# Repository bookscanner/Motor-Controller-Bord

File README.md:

# bookscanner
design of an affordable bookscanner for African universities

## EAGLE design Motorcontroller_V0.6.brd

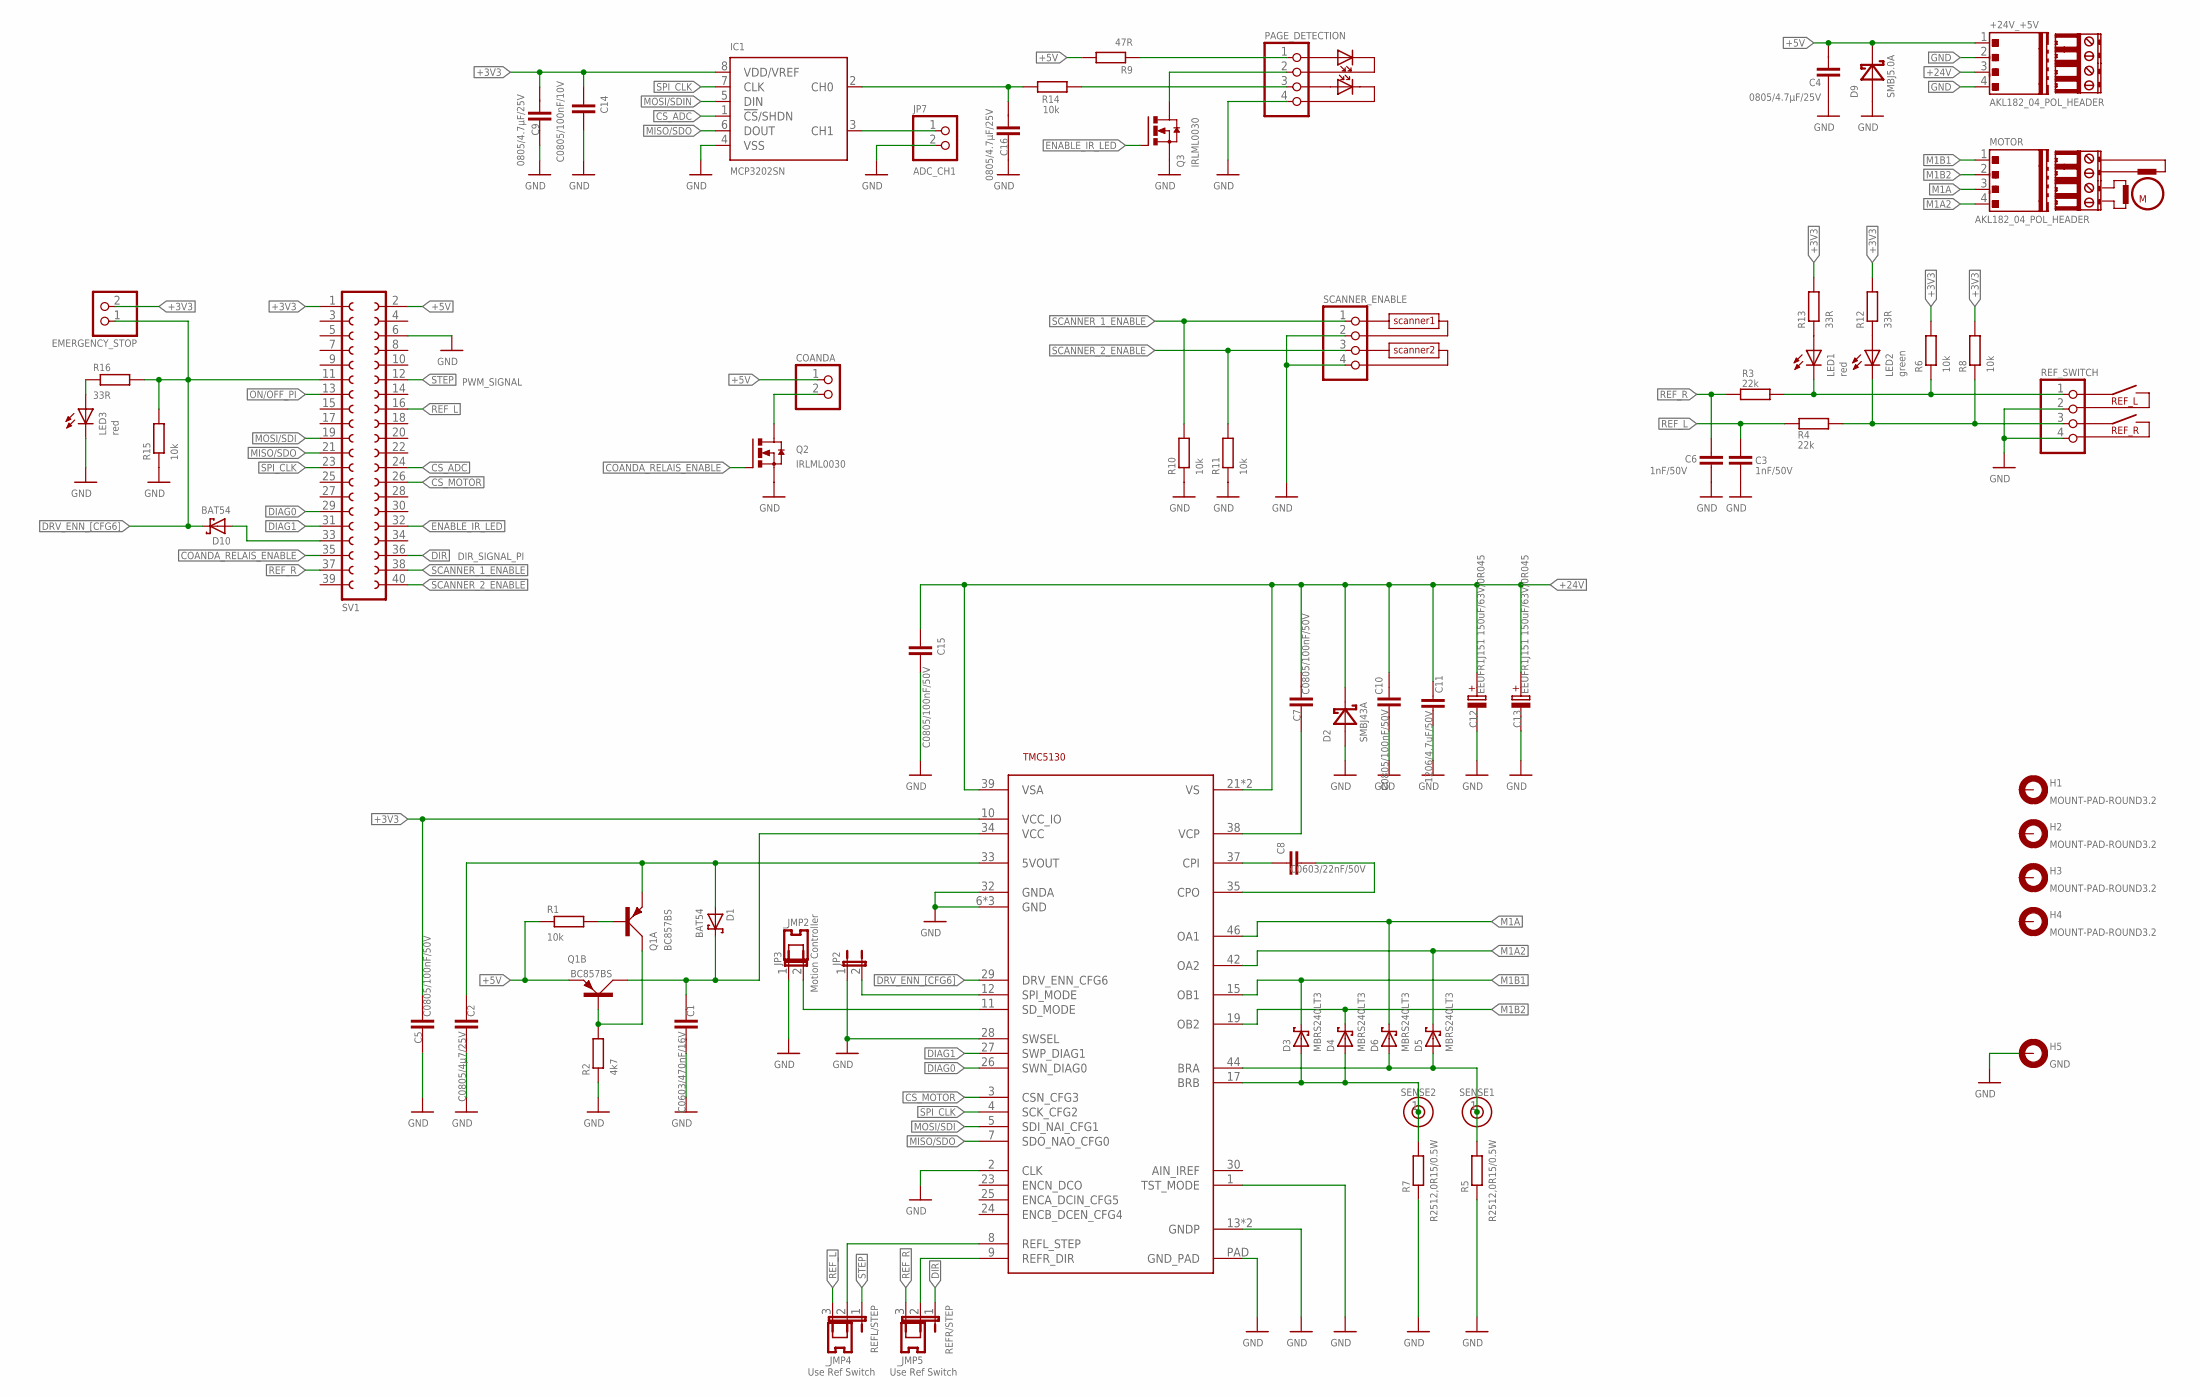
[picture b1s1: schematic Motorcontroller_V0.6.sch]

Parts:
+24V_+5V: AKL182_04_POL_HEADER; AKL169_04_POL
C1: C0603/470nF/16V; 0603
C2: C0805/4µ7/25V; 0805
C3, C6: 1nF/50V; C0603K
C4, C9, C16: 0805/4.7µF/25V; RCL_0805
C5, C7, C10: C0805/100nF/50V; 0805
C8: C0603/22nF/50V; C0603
C11: 1206/4.7uF/50V; C1206
C12, C13: EEUFR1J151 150uF/63V/0R045; C_POL_RAD_THT_5X10X12.5
C14: C0805/100nF/10V; C0805
C15: C0805/100nF/50V; C0805
COANDA: PINHD-1X2; 1X02
D1, D10: BAT54; SOT23
D2: SMBJ43A; SMB
D3, D4, D5, D6: MBRS240LT3; SMB
D9: SMBJ5.0A; SMB
EMERGENCY_STOP: PINHD-1X2; 1X02
H1, H2, H3, H4: MOUNT-PAD-ROUND3.2; 3,2-PAD
H5: GND; 3,2-PAD
IC1: MCP3202SN; SO-08
JP2, JP3: JP1E; JP1
JP7: ADC_CH1; 1X02
LED1, LED3: red; CHIP-LED0805
LED2: green; CHIP-LED0805
MOTOR: AKL182_04_POL_HEADER; AKL169_04_POL
PAGE_DETECTION: PINHD-1X4; 1X04
Q1: BC857BS; SOT363_PHILIPS
Q2, Q3: IRLML0030; SOT-23
R1, R6, R8, R10, R11, R14, R15: 10k; M0805
R2: 4k7; M0805
R3, R4: 22k; R0603
R5, R7: R2512,0R15/0.5W; R2512
R9: 47R; M1206
R12, R13, R16: 33R; M0805
REFL/STEP: JP2E; JP2
REFR/STEP: JP2E; JP2
REF_SWITCH: PINHD-1X4; 1X04
SCANNER_ENABLE: PINHD-1X4; 1X04
SENSE1, SENSE2: 1PIN_1ROW; 1PIN_1ROW_THT
SV1: FE20-2
TERM1, TERM3: AKL182_04_POL_TERMINAL; EXTRA_TERMINAL
TMC5130: TMC5130; QFP50P900X900X113-49N_NOFID

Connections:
+3V3: C5.1, C9.1, C14.2, EMERGENCY_STOP.2, IC1.8 (VDD/VREF), R6.2, R8.2, R12.2, R13.2, SV1.1, TMC5130.10 (VCC_IO)
+5V: +24V_+5V.1, C4.1, COANDA.1, D9.C, Q1.4 (E), R1.1, R9.2, SV1.2
+24V: +24V_+5V.3, C7.1, C10.2, C11.1, C12.+, C13.+, C15.2, D2.C, TMC5130.21 (VS), TMC5130.39 (VSA), TMC5130.40 (VS)
COANDA_RELAIS_ENABLE: Q2.1 (G), SV1.35
CS_ADC: IC1.1 (!CS!/SHDN), SV1.24
CS_MOTOR: SV1.26, TMC5130.3 (CSN_CFG3)
DIAG0: SV1.29, TMC5130.26 (SWN_DIAG0)
DIAG1: SV1.31, TMC5130.27 (SWP_DIAG1)
DIR: REFR/STEP.1, SV1.36
DRV_ENN_[CFG6]: D10.3 (C), EMERGENCY_STOP.1, R15.2, R16.2, SV1.11, TMC5130.29 (DRV_ENN_CFG6)
ENABLE_IR_LED: Q3.1 (G), SV1.32
GND: +24V_+5V.2, +24V_+5V.4, C1.1, C2.1, C3.1, C4.2, C5.2, C6.1, C9.2, C10.1, C11.2, C12.-, C13.-, C14.1, C15.1, C16.2, D2.A, D9.A, H5.B3,2, IC1.4 (VSS), JP2.1, JP3.1, JP7.2, LED3.C, PAGE_DETECTION.4, Q2.2 (S), Q3.2 (S), R2.1, R5.1, R7.1, R10.1, R11.1, R15.1, REF_SWITCH.2, REF_SWITCH.4, SCANNER_ENABLE.2, SCANNER_ENABLE.4, SV1.6, TMC5130.1 (TST_MODE), TMC5130.2 (CLK), TMC5130.6 (GND), TMC5130.13 (GNDP), TMC5130.28 (SWSEL), TMC5130.31 (GND), TMC5130.32 (GNDA), TMC5130.36 (GND), TMC5130.48 (GNDP), TMC5130.PAD (GND_PAD)
GND1: COANDA.2, Q2.3 (D)
M1A: D6.C, MOTOR.3, TMC5130.46 (OA1)
M1A2: D5.C, MOTOR.4, TMC5130.42 (OA2)
M1B1: D3.C, MOTOR.1, TMC5130.15 (OB1)
M1B2: D4.C, MOTOR.2, TMC5130.19 (OB2)
MISO/SDO: IC1.6 (DOUT), SV1.21, TMC5130.7 (SDO_NAO_CFG0)
MOSI/SDI: SV1.19, TMC5130.5 (SDI_NAI_CFG1)
MOSI/SDIN: IC1.5 (DIN)
unnamed: Q1.5 (B), Q1.6 (C), R2.2
unnamed: C1.2, D1.3 (C), Q1.3 (C), TMC5130.34 (VCC)
unnamed: JP2.2, TMC5130.12 (SPI_MODE)
unnamed: Q1.2 (B), R1.2
unnamed: JP3.2, TMC5130.11 (SD_MODE)
unnamed: D10.1 (A), SV1.33
unnamed: LED3.A, R16.1
unnamed: C8.1, TMC5130.37 (CPI)
unnamed: C8.2, TMC5130.35 (CPO)
unnamed: C7.2, TMC5130.38 (VCP)
unnamed: PAGE_DETECTION.2, Q3.3 (D)
unnamed: C2.2, D1.1 (A), Q1.1 (E), TMC5130.33 (5VOUT)
unnamed: REFR/STEP.2, TMC5130.9 (REFR_DIR)
unnamed: REFL/STEP.2, TMC5130.8 (REFL_STEP)
unnamed: LED2.C, R4.2, R8.1, REF_SWITCH.3
unnamed: LED1.C, R3.2, R6.1, REF_SWITCH.1
unnamed: LED2.A, R12.1
unnamed: LED1.A, R13.1
unnamed: C16.1, IC1.2 (CH0), R14.2
unnamed: IC1.3 (CH1), JP7.1
unnamed: PAGE_DETECTION.3, R14.1
unnamed: PAGE_DETECTION.1, R9.1
ON/OFF_PI: SV1.13
REF_L: C3.2, R4.1, REFL/STEP.3, SV1.16
REF_R: C6.2, R3.1, REFR/STEP.3, SV1.37
SCANNER_1_ENABLE: R10.2, SCANNER_ENABLE.1, SV1.38
SCANNER_2_ENABLE: R11.2, SCANNER_ENABLE.3, SV1.40
SENSE1: D5.A, D6.A, R5.2, SENSE1.1, TMC5130.44 (BRA)
SENSE2: D3.A, D4.A, R7.2, SENSE2.1, TMC5130.17 (BRB)
SPI_CLK: IC1.7 (CLK), SV1.23, TMC5130.4 (SCK_CFG2)
STEP: REFL/STEP.1, SV1.12

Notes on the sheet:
REF_L
REF_R
scanner1
scanner2
PWM_SIGNAL
DIR_SIGNAL_PI

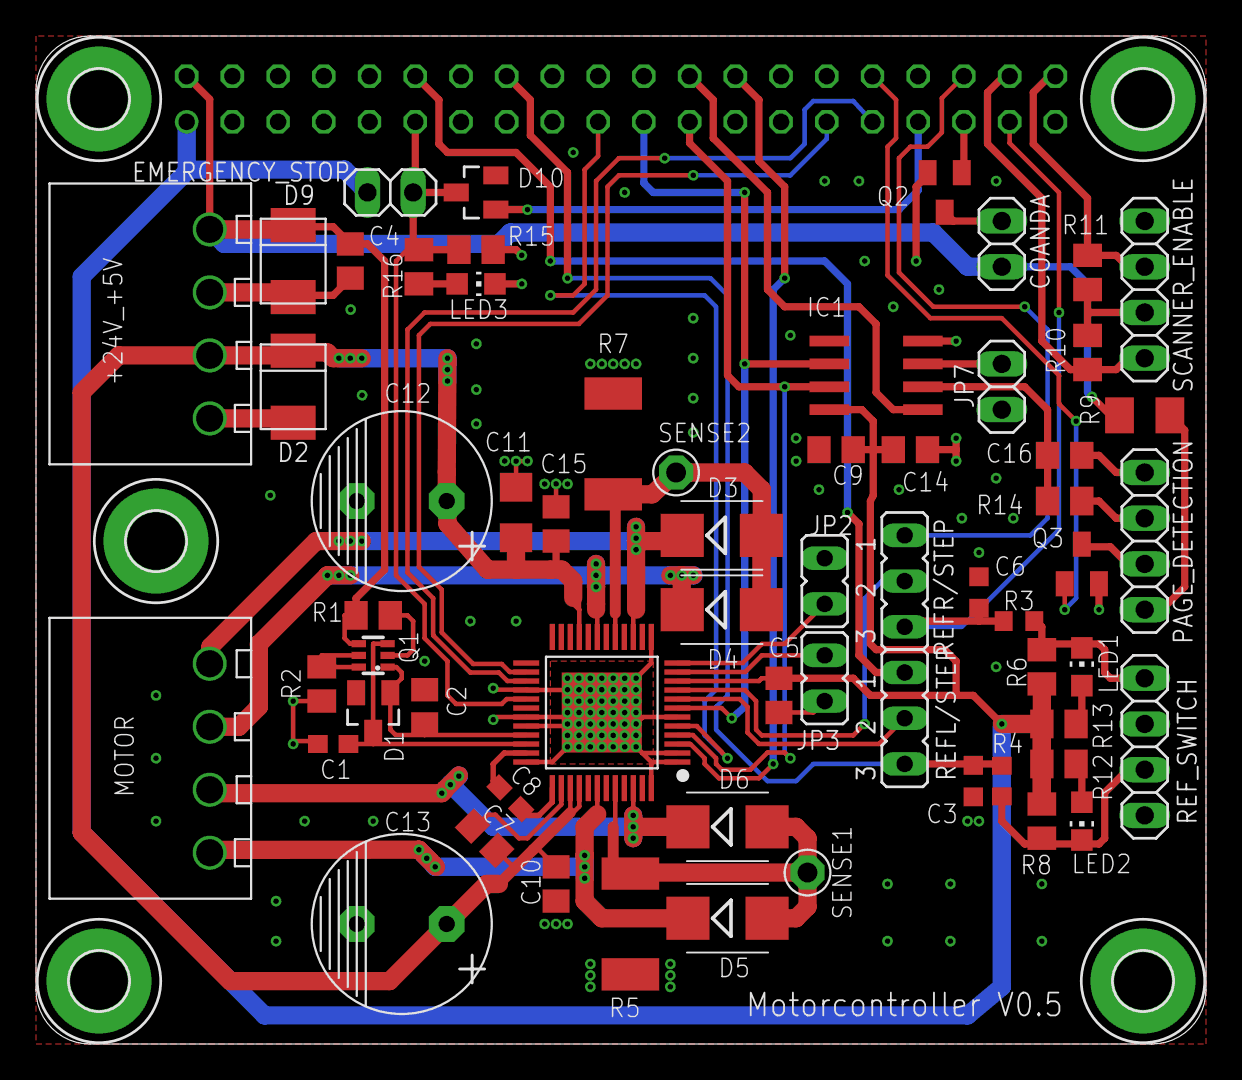
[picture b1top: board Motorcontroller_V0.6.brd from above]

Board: 2 copper layers, 65.0 x 56.0 mm, 70 parts (1 on the bottom side), 49 nets.

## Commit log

2016-06-21 Add files via upload
    Schematic and layout of the Motorcontroller version 0.6
